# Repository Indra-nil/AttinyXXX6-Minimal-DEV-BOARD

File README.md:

# AttinyXXX6-Minimal-DEV-BOARD

This series dev boards are compatible for tinyAVR 0 Series(Attiny406, Attiny806, Attiny1606), tinyAVR 1 Series(Attiny416, Attiny816, Attiny1616, Attiny3216), tinyAVR 2 Series(Attiny426, Attiny826, Attiny1626, Attiny3226) microcontrollers(VQFN-20).

This is a bare minium pcb. For programing, need any kind of UPDI programmer(jtag2Updi, pyupdi, edbg or atmel ICE) and programs can be written on either Arduino or AVR-GCC.

Some useful links
--------------------

[jtag2updi](https://github.com/ElTangas/jtag2updi.git) 

[pyupdi](https://github.com/mraardvark/pyupdi.git)

[Various UPDI hardwares](https://github.com/wagiminator/AVR-Programmer.git)

[megaTinyCore(arduino core)](https://github.com/SpenceKonde/megaTinyCore.git)

[TinyCore(arduino core)](https://github.com/xukangmin/TinyCore.git)

[Microchip Studio for AVR](https://www.microchip.com/en-us/tools-resources/develop/microchip-studio)

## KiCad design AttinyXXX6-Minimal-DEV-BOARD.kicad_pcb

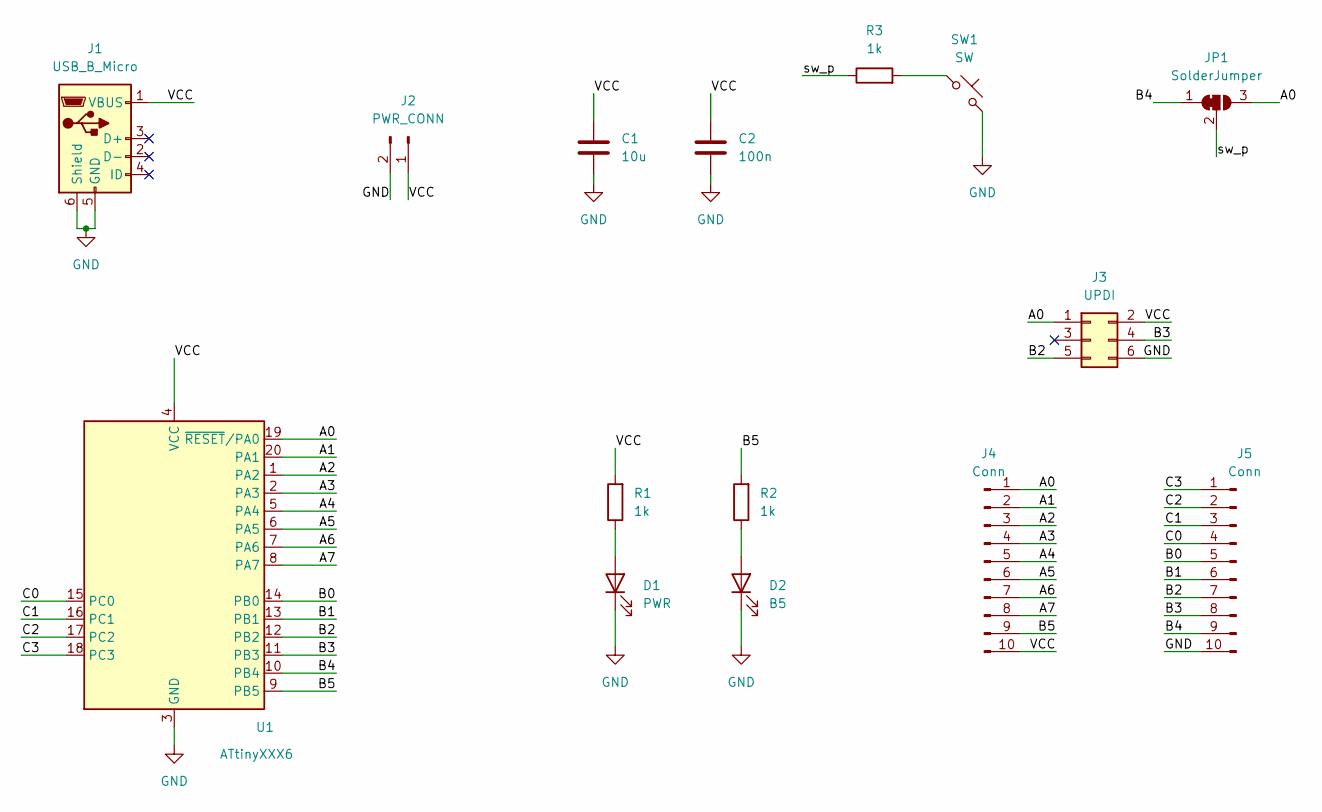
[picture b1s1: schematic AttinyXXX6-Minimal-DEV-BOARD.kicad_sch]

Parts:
C1: 10u; C_0603_1608Metric
C2: 100n; C_0603_1608Metric
D1: PWR; LED_0603_1608Metric
D2: B5; LED_0603_1608Metric
J1: USB_B_Micro; MUP-U513
J2: PWR_CONN; PinHeader_1x02_P2.54mm_Vertical
J3: UPDI; PinHeader_2x03_P2.54mm_Vertical
J4, J5: Conn; PinHeader_1x10_P2.54mm_Vertical
JP1: SolderJumper; SolderJumper-3_P1.3mm_Bridged12_Pad1.0x1.5mm_NumberLabels
R1, R2: 1k; R_0603_1608Metric
R3: 1k; R_0402_1005Metric
SW1: SW; SW_Push_SPST_NO_Alps_SKRK
U1: ATtinyXXX6; VQFN-20-1EP_3x3mm_P0.4mm_EP1.7x1.7mm

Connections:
/A0: J3.1, J4.1, JP1.3 (B), U1.19 (~RESET/PA0)
/A1: J4.2, U1.20 (PA1)
/A2: J4.3, U1.1 (PA2)
/A3: J4.4, U1.2 (PA3)
/A4: J4.5, U1.5 (PA4)
/A5: J4.6, U1.6 (PA5)
/A6: J4.7, U1.7 (PA6)
/A7: J4.8, U1.8 (PA7)
/B0: J5.5, U1.14 (PB0)
/B1: J5.6, U1.13 (PB1)
/B2: J3.5, J5.7, U1.12 (PB2)
/B3: J3.4, J5.8, U1.11 (PB3)
/B4: J5.9, JP1.1 (A), U1.10 (PB4)
/B5: J4.9, R2.2, U1.9 (PB5)
/C0: J5.4, U1.15 (PC0)
/C1: J5.3, U1.16 (PC1)
/C2: J5.2, U1.17 (PC2)
/C3: J5.1, U1.18 (PC3)
/VCC: C1.1, C2.1, J1.1 (VBUS), J2.1, J3.2, J4.10, R1.2, U1.4 (VCC)
/sw_p: JP1.2 (C), R3.1
GND: C1.2, C2.2, D1.1 (K), D2.1 (K), J1.5 (GND), J1.6 (Shield), J2.2, J3.6, J5.10, SW1.2, U1.3 (GND), U1.21 (GND)
unnamed: D1.2 (A), R1.1
unnamed: D2.2 (A), R2.1
unnamed: R3.2, SW1.1

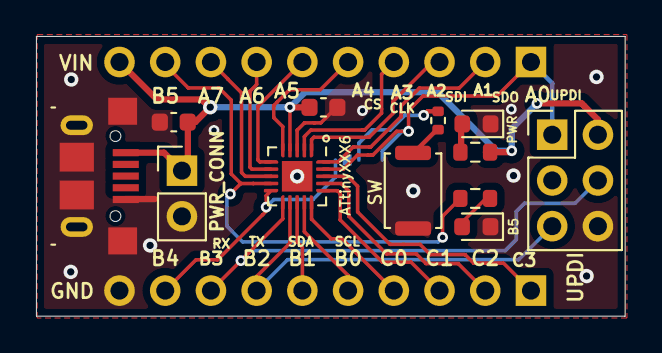
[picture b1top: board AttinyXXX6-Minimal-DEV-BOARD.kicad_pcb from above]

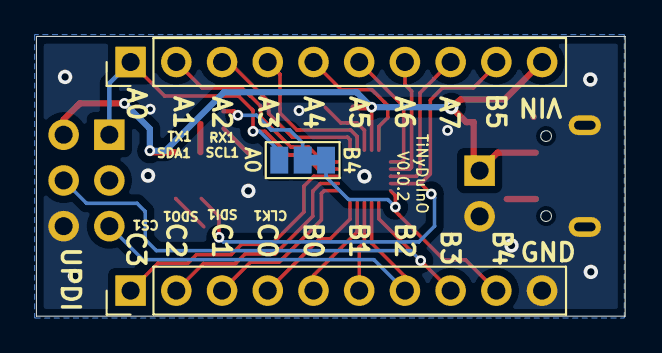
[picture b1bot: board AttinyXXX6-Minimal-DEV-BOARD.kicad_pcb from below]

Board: 2 copper layers, 32.7 x 15.5 mm, 15 parts (3 on the bottom side), 24 nets.

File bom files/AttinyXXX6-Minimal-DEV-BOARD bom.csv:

Ref,Qnty,Value,Cmp name,Footprint,MPN
"C1, ",1,10u,C,Capacitor_SMD:C_0603_1608Metric,CC0603KRX5R6BB106
"C2, ",1,100n,C,Capacitor_SMD:C_0603_1608Metric,CC0603KRX7R9BB104
"D1, ",1,PWR,LED,LED_SMD:LED_0603_1608Metric,19-217/R6C-AL1M2VY/3T 
"D2, ",1,B5,LED,LED_SMD:LED_0603_1608Metric,19-217/G7C-AN1P2/3T
"J1, ",1,USB_B_Micro,USB_B_Micro,MUP-U513:MUP-U513,MUP-U513
"J2, ",1,PWR_CONN,Conn_01x02_Male,Connector_PinHeader_2.54mm:PinHeader_1x02_P2.54mm_Vertical,
"J3, ",1,UPDI,Conn_02x03_Odd_Even,Connector_PinHeader_2.54mm:PinHeader_2x03_P2.54mm_Vertical,
"J4, J5, ",2,Conn,Conn_01x10_Male,Connector_PinHeader_2.54mm:PinHeader_1x10_P2.54mm_Vertical,
"R1, R2, ",2,1k,R,Resistor_SMD:R_0603_1608Metric,RC0603FR-071KL
"R3, ",1,1k,R,Resistor_SMD:R_0402_1005Metric,RC0402JR-071KL
"SW1, ",1,SW,SW_Push_45deg,Button_Switch_SMD:SW_Push_SPST_NO_Alps_SKRK,SKRKAEE020
"U1, ",1,ATtinyXXX6,ATtiny1616-M,Package_DFN_QFN:VQFN-20-1EP_3x3mm_P0.4mm_EP1.7x1.7mm,ATTINY1616-MN

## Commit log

2022-05-12 initial release
2022-10-10 pinout and updi
    PIN B0 location change and UPDI connector pin change to universal one.
2022-10-10 B0 location and UPDI connector
    PIN B0 location change and UPDI connector changing to universal one
